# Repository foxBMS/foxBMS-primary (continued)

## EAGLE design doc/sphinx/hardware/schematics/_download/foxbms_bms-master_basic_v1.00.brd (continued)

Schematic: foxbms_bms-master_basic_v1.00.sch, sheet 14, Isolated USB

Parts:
C1401, C1406: 4.7µ; C0603
C1402, C1403, C1404, C1405, C1407, C1408, C1409, C1410: 100n; C0603
IC1401, IC1404: IP4220CZ6; D_SMD_TSOP6_(SOT457/SC-74)_R_NXP_REV01
IC1402, IC1405: FT231XS-R; IC_SMD_SSOP-20_R_FTDI_REV01
IC1403, IC1406: ADUM1401ARW; IC_SMD_SOIC-16_(JEDEC_MS-013-AA)_R_ANALOG_REV01
R1401, R1402, R1405, R1406: 27; 0603
R1403, R1404, R1407, R1408: 0; 0603
X1401, X1402: MINI-USB-2.0; X_SMD_MINI-USB-2.0-TYPAB_R_MULTICOMP_REV01

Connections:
+3.3V_0: C1405.1, IC1403.10 (VE2), IC1403.16 (VDD2); also elsewhere on the board
+3.3V_1: C1410.1, IC1406.10 (VE2), IC1406.16 (VDD2); also elsewhere on the board
DM: IC1401.4 (I/O3), R1401.2, X1401.2
DM1: IC1404.4 (I/O3), R1405.2, X1402.2
DP: IC1401.6 (I/O4), R1402.2, X1401.3
DP1: IC1404.6 (I/O4), R1406.2, X1402.3
FTDI_MCU_0_DTR: IC1403.13 (VOB); also elsewhere on the board
FTDI_MCU_0_RTS: IC1403.14 (VOA); also elsewhere on the board
FTDI_MCU_0_RX: IC1403.12 (VOC); also elsewhere on the board
FTDI_MCU_0_TX: IC1403.11 (VID); also elsewhere on the board
FTDI_MCU_1_DTR: IC1406.13 (VOB); also elsewhere on the board
FTDI_MCU_1_RTS: IC1406.14 (VOA); also elsewhere on the board
FTDI_MCU_1_RX: IC1406.12 (VOC); also elsewhere on the board
FTDI_MCU_1_TX: IC1406.11 (VID); also elsewhere on the board
GND_0: C1405.2, IC1403.9 (GND2), IC1403.15 (GND2); also elsewhere on the board
GND_1: C1410.2, IC1406.9 (GND2), IC1406.15 (GND2); also elsewhere on the board
unnamed: IC1402.11 (USBDP), R1402.1
unnamed: IC1402.12 (USBDM), R1401.1
unnamed: IC1405.11 (USBDP), R1406.1
unnamed: IC1405.12 (USBDM), R1405.1
unnamed: IC1402.20 (TXD), IC1403.5 (VIC)
unnamed: IC1405.20 (TXD), IC1406.5 (VIC)
unnamed: IC1405.4 (RXD), IC1406.6 (VOD)
unnamed: IC1405.2 (RTS#), IC1406.3 (VIA)
unnamed: IC1405.1 (DTR#), IC1406.4 (VIB)
unnamed: IC1402.4 (RXD), IC1403.6 (VOD)
unnamed: IC1402.1 (DTR#), IC1403.4 (VIB)
unnamed: C1409.1, IC1405.3 (VCCIO), IC1405.13 (3V3OUT), IC1405.14 (RESET#)
unnamed: IC1405.9 (CTS#), R1407.1
unnamed: IC1402.2 (RTS#), IC1403.3 (VIA)
unnamed: IC1405.7 (DSR#), R1408.1
unnamed: IC1402.9 (CTS#), R1403.1
unnamed: IC1402.7 (DSR#), R1404.1
USB_0_GND_EXT: C1401.2, C1402.2, C1403.2, C1404.2, IC1401.2 (GND), IC1402.6 (GND1), IC1402.16 (GND2), IC1403.2 (GND1), IC1403.8 (GND1), R1403.2, R1404.2, X1401.5
USB_0_VBUS1_EXT: C1401.1, C1402.1, C1403.1, IC1401.5 (VP), IC1402.15 (VCC), IC1403.1 (VDD1), IC1403.7 (VE1), X1401.1
USB_0_VCC_EXT: C1404.1, IC1402.3 (VCCIO), IC1402.13 (3V3OUT), IC1402.14 (RESET#)
USB_GND_0_EXT1: C1406.2, C1407.2, C1408.2, C1409.2, IC1404.2 (GND), IC1405.6 (GND1), IC1405.16 (GND2), IC1406.2 (GND1), IC1406.8 (GND1), R1407.2, R1408.2, X1402.5
USB_VBUS1_0_EXT1: C1406.1, C1407.1, C1408.1, IC1404.5 (VP), IC1405.15 (VCC), IC1406.1 (VDD1), IC1406.7 (VE1), X1402.1

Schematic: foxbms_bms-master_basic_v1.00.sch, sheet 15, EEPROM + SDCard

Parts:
C1501: 100n; 0603
IC1501: AT25128B-SSHL-T; IC_SMD_SOIC-8_R_ATMEL_REV01
R1501, R1502: 10k; 0603

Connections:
+3.3V_0: C1501.2, IC1501.8 (VCC), R1501.2, R1502.2; also elsewhere on the board
DATA_STORAGE_SPI_EEPROM_CS: IC1501.1 (!CS); also elsewhere on the board
DATA_STORAGE_SPI_MISO: IC1501.2 (SO); also elsewhere on the board
DATA_STORAGE_SPI_MOSI: IC1501.5 (SI); also elsewhere on the board
DATA_STORAGE_SPI_SCK: IC1501.6 (SCK); also elsewhere on the board
GND_0: C1501.1, IC1501.4 (GND); also elsewhere on the board
unnamed: IC1501.7 (HOLD), R1501.1
unnamed: IC1501.3 (!WP), R1502.1

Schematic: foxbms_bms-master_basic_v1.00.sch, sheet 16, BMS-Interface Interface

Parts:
C1601, C1602, C1603, C1604: 100n; C0603
SV1601, SV1603: MA04-2
SV1602, SV1604: MA08-2
X1601: 43045-1600_MOLEX_16PIN; X_TH_MOLEX_43045-1600_R_REV01

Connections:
+3.3V_0: C1601.1, SV1602.3; also elsewhere on the board
+3.3V_1: C1603.1, SV1604.3; also elsewhere on the board
+5.0V_0: C1602.1, SV1602.4; also elsewhere on the board
+5.0V_1: C1604.1, SV1604.4; also elsewhere on the board
BMS-INTERFACE_0_GPIO_0: SV1602.11; also elsewhere on the board
BMS-INTERFACE_0_GPIO_1: SV1602.12; also elsewhere on the board
BMS-INTERFACE_0_GPIO_2: SV1602.2; also elsewhere on the board
BMS-INTERFACE_0_GPIO_3: SV1602.1; also elsewhere on the board
BMS-INTERFACE_0_SPI_CS: SV1602.8; also elsewhere on the board
BMS-INTERFACE_0_SPI_MISO: SV1602.6; also elsewhere on the board
BMS-INTERFACE_0_SPI_MOSI: SV1602.5; also elsewhere on the board
BMS-INTERFACE_0_SPI_SCK: SV1602.7; also elsewhere on the board
BMS-INTERFACE_1_GPIO_0: SV1604.11; also elsewhere on the board
BMS-INTERFACE_1_GPIO_1: SV1604.12; also elsewhere on the board
BMS-INTERFACE_1_GPIO_2: SV1604.2; also elsewhere on the board
BMS-INTERFACE_1_GPIO_3: SV1604.1; also elsewhere on the board
BMS-INTERFACE_1_SPI_CS: SV1604.8; also elsewhere on the board
BMS-INTERFACE_1_SPI_MISO: SV1604.6; also elsewhere on the board
BMS-INTERFACE_1_SPI_MOSI: SV1604.5; also elsewhere on the board
BMS-INTERFACE_1_SPI_SCK: SV1604.7; also elsewhere on the board
GND_0: C1601.2, C1602.2, SV1602.9, SV1602.10; also elsewhere on the board
GND_1: C1603.2, C1604.2, SV1604.9, SV1604.10; also elsewhere on the board
unnamed: SV1601.1, X1601.1
unnamed: SV1601.2, X1601.9
unnamed: SV1601.3, X1601.2
unnamed: SV1601.4, X1601.10
unnamed: SV1601.5, X1601.3
unnamed: SV1601.6, X1601.11
unnamed: SV1601.7, X1601.4
unnamed: SV1601.8, X1601.12
unnamed: SV1603.1, X1601.5
unnamed: SV1603.3, X1601.6
unnamed: SV1603.5, X1601.7
unnamed: SV1603.7, X1601.8
unnamed: SV1603.2, X1601.13
unnamed: SV1603.4, X1601.14
unnamed: SV1603.6, X1601.15
unnamed: SV1603.8, X1601.16

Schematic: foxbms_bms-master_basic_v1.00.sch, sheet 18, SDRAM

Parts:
C1801, C1802, C1803, C1804, C1805, C1806, C1807: 100n; C0603
IC1801: IS42S16400J-5TL; IC_SMD_TSOP-II_(54-PIN)_R_ISSI_REV01

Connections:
+3.3V_0: C1801.1, C1802.1, C1803.1, C1804.1, C1805.1, C1806.1, C1807.1, IC1801.1 (VDD), IC1801.3 (VDDQ), IC1801.9 (VDDQ), IC1801.14 (VDD), IC1801.27 (VDD), IC1801.43 (VDDQ), IC1801.49 (VDDQ); also elsewhere on the board
FMC_MCU_0_RAM_A0: IC1801.23 (A0); also elsewhere on the board
FMC_MCU_0_RAM_A1: IC1801.24 (A1); also elsewhere on the board
FMC_MCU_0_RAM_A2: IC1801.25 (A2); also elsewhere on the board
FMC_MCU_0_RAM_A3: IC1801.26 (A3); also elsewhere on the board
FMC_MCU_0_RAM_A4: IC1801.29 (A4); also elsewhere on the board
FMC_MCU_0_RAM_A5: IC1801.30 (A5); also elsewhere on the board
FMC_MCU_0_RAM_A6: IC1801.31 (A6); also elsewhere on the board
FMC_MCU_0_RAM_A7: IC1801.32 (A7); also elsewhere on the board
FMC_MCU_0_RAM_A8: IC1801.33 (A8); also elsewhere on the board
FMC_MCU_0_RAM_A9: IC1801.34 (A9); also elsewhere on the board
FMC_MCU_0_RAM_A10: IC1801.22 (A10); also elsewhere on the board
FMC_MCU_0_RAM_A11: IC1801.35 (A11); also elsewhere on the board
FMC_MCU_0_RAM_BA0: IC1801.20 (BA0); also elsewhere on the board
FMC_MCU_0_RAM_BA1: IC1801.21 (BA1); also elsewhere on the board
FMC_MCU_0_RAM_D0: IC1801.2 (DQ0); also elsewhere on the board
FMC_MCU_0_RAM_D1: IC1801.4 (DQ1); also elsewhere on the board
FMC_MCU_0_RAM_D2: IC1801.5 (DQ2); also elsewhere on the board
FMC_MCU_0_RAM_D3: IC1801.7 (DQ3); also elsewhere on the board
FMC_MCU_0_RAM_D4: IC1801.8 (DQ4); also elsewhere on the board
FMC_MCU_0_RAM_D5: IC1801.10 (DQ5); also elsewhere on the board
FMC_MCU_0_RAM_D6: IC1801.11 (DQ6); also elsewhere on the board
FMC_MCU_0_RAM_D7: IC1801.13 (DQ7); also elsewhere on the board
FMC_MCU_0_RAM_D8: IC1801.42 (DQ8); also elsewhere on the board
FMC_MCU_0_RAM_D9: IC1801.44 (DQ9); also elsewhere on the board
FMC_MCU_0_RAM_D10: IC1801.45 (DQ10); also elsewhere on the board
FMC_MCU_0_RAM_D11: IC1801.47 (DQ11); also elsewhere on the board
FMC_MCU_0_RAM_D12: IC1801.48 (DQ12); also elsewhere on the board
FMC_MCU_0_RAM_D13: IC1801.50 (DQ13); also elsewhere on the board
FMC_MCU_0_RAM_D14: IC1801.51 (DQ14); also elsewhere on the board
FMC_MCU_0_RAM_D15: IC1801.53 (DQ15); also elsewhere on the board
FMC_MCU_0_RAM_NBL0: IC1801.15 (LDQM); also elsewhere on the board
FMC_MCU_0_RAM_NBL1: IC1801.39 (UDQM); also elsewhere on the board
FMC_MCU_0_RAM_SDCKE1: IC1801.37 (CKE); also elsewhere on the board
FMC_MCU_0_RAM_SDCLK: IC1801.38 (CLK); also elsewhere on the board
FMC_MCU_0_RAM_SDNCAS: IC1801.17 (!CAS); also elsewhere on the board
FMC_MCU_0_RAM_SDNE1: IC1801.19 (!CS); also elsewhere on the board
FMC_MCU_0_RAM_SDNRAS: IC1801.18 (!RAS); also elsewhere on the board
FMC_MCU_0_RAM_SDNWE: IC1801.16 (!WE); also elsewhere on the board
GND_0: C1801.2, C1802.2, C1803.2, C1804.2, C1805.2, C1806.2, C1807.2, IC1801.6 (GNDQ), IC1801.12 (GNDQ), IC1801.28 (GND), IC1801.41 (GND), IC1801.46 (GNDQ), IC1801.52 (GNDQ), IC1801.54 (GND); also elsewhere on the board

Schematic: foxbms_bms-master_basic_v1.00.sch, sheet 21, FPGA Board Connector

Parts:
C2101, C2102: 100n; C0603
SV2101: MA04-2

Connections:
+3.3V_0: C2101.2, SV2101.1; also elsewhere on the board
+5.0V_0: C2102.1, SV2101.2; also elsewhere on the board
GND_0: C2101.1, C2102.2, SV2101.5, SV2101.6; also elsewhere on the board
MCU_TO_FPGA_INTERFACE_MCU_0_CS: SV2101.8; also elsewhere on the board
MCU_TO_FPGA_INTERFACE_MCU_0_MISO: SV2101.3; also elsewhere on the board
MCU_TO_FPGA_INTERFACE_MCU_0_MOSI: SV2101.7; also elsewhere on the board
MCU_TO_FPGA_INTERFACE_MCU_0_SCK: SV2101.4; also elsewhere on the board

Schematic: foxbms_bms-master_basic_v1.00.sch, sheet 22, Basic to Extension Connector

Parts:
JP2201, JP2202: PINHD-2X12; 2X12

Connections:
+3.3V_0: JP2201.1, JP2201.3, JP2202.1, JP2202.3; also elsewhere on the board
ADC_MCU_0_CH_0: JP2202.8; also elsewhere on the board
ADC_MCU_0_CH_1: JP2202.7; also elsewhere on the board
ADC_MCU_0_CH_2: JP2202.6; also elsewhere on the board
ADC_MCU_0_CH_3: JP2202.5; also elsewhere on the board
ADC_MCU_0_CH_4: JP2202.9; also elsewhere on the board
CAN_1_RX: JP2201.6; also elsewhere on the board
CAN_1_TRANS_STANDBY_CONTROL: JP2201.5; also elsewhere on the board
CAN_1_TX: JP2201.7; also elsewhere on the board
CONTACTOR_6_CONTROL: JP2201.18; also elsewhere on the board
CONTACTOR_6_FEEDBACK: JP2201.17; also elsewhere on the board
CONTACTOR_7_CONTROL: JP2201.16; also elsewhere on the board
CONTACTOR_7_FEEDBACK: JP2201.15; also elsewhere on the board
CONTACTOR_8_CONTROL: JP2202.10; also elsewhere on the board
CONTACTOR_8_FEEDBACK: JP2202.11; also elsewhere on the board
DATA_STORAGE_SPI_MISO: JP2201.21; also elsewhere on the board
DATA_STORAGE_SPI_MOSI: JP2201.19; also elsewhere on the board
DATA_STORAGE_SPI_SCK: JP2201.20; also elsewhere on the board
DATA_STORAGE_SPI_SDCARD_NSS: JP2201.23; also elsewhere on the board
GND_0: JP2201.2, JP2201.4, JP2202.2, JP2202.4; also elsewhere on the board
ISONOC_0_CONTROL: JP2202.16; also elsewhere on the board
ISONOC_1_CONTROL: JP2202.17; also elsewhere on the board
ISONOC_2_CONTROL: JP2202.18; also elsewhere on the board
ISONOC_3_CONTROL: JP2202.19; also elsewhere on the board
ISONOC_4_CONTROL: JP2202.20; also elsewhere on the board
ISONOC_5_CONTROL: JP2202.21; also elsewhere on the board
ISO_GPIO_MCU_0_IN_0: JP2202.22; also elsewhere on the board
ISO_GPIO_MCU_0_IN_1: JP2202.23; also elsewhere on the board
ISO_GPIO_MCU_0_IN_2: JP2201.13; also elsewhere on the board
ISO_GPIO_MCU_0_IN_3: JP2201.10; also elsewhere on the board
ISO_GPIO_MCU_0_OUT_0: JP2201.9; also elsewhere on the board
ISO_GPIO_MCU_0_OUT_1: JP2201.14; also elsewhere on the board
ISO_GPIO_MCU_0_OUT_2: JP2201.11; also elsewhere on the board
ISO_GPIO_MCU_0_OUT_3: JP2201.12; also elsewhere on the board
RS485_MCU_0_DE: JP2202.15; also elsewhere on the board
RS485_MCU_0_NRE: JP2202.14; also elsewhere on the board
RS485_MCU_0_RX: JP2202.13; also elsewhere on the board
RS485_MCU_0_TX: JP2202.12; also elsewhere on the board
SDCARD_SUPPLY_CONTROL: JP2201.22; also elsewhere on the board

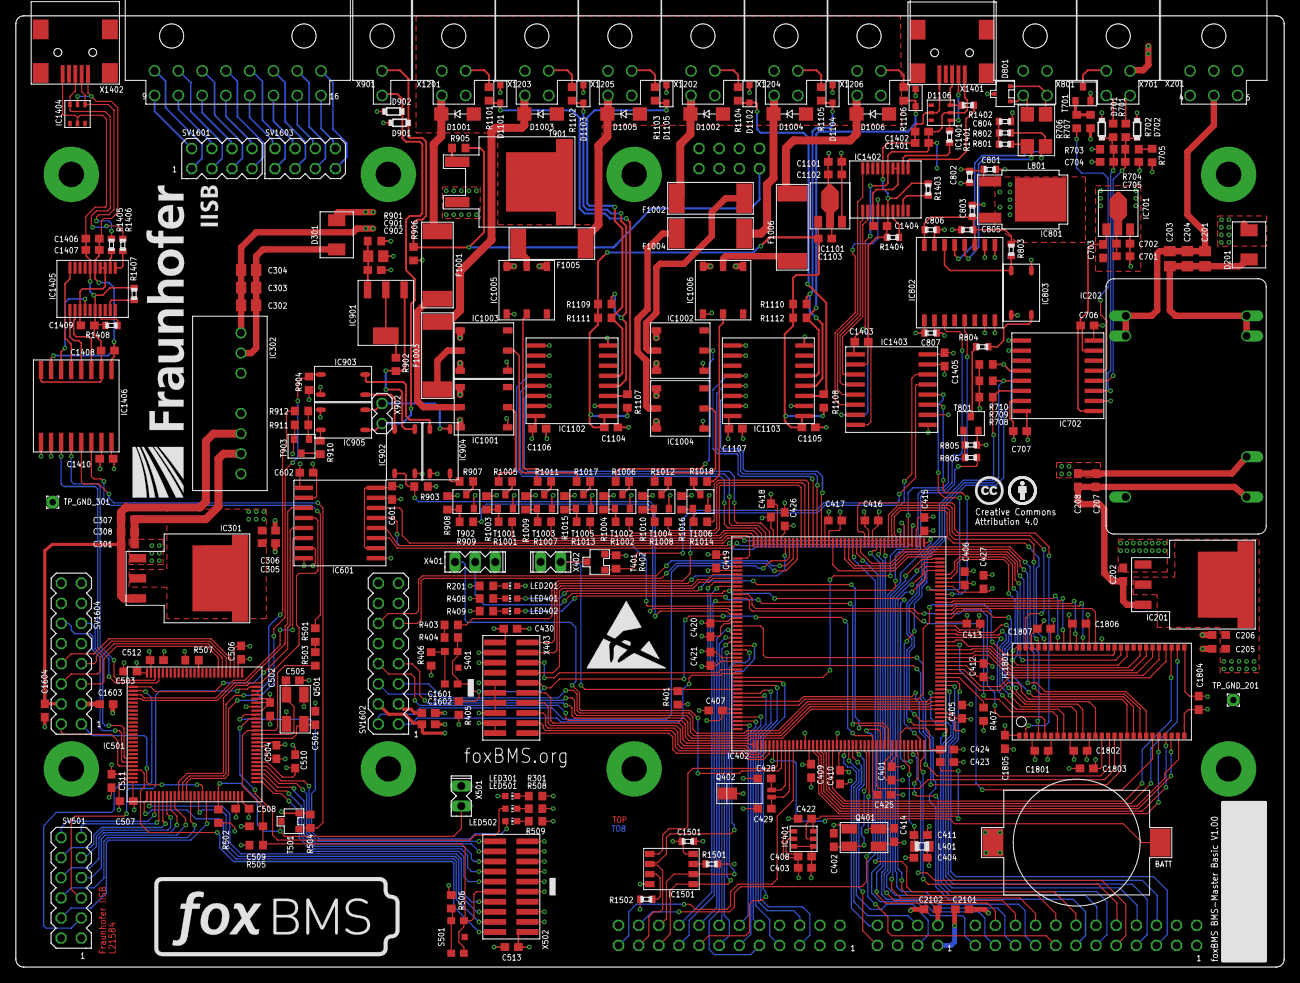
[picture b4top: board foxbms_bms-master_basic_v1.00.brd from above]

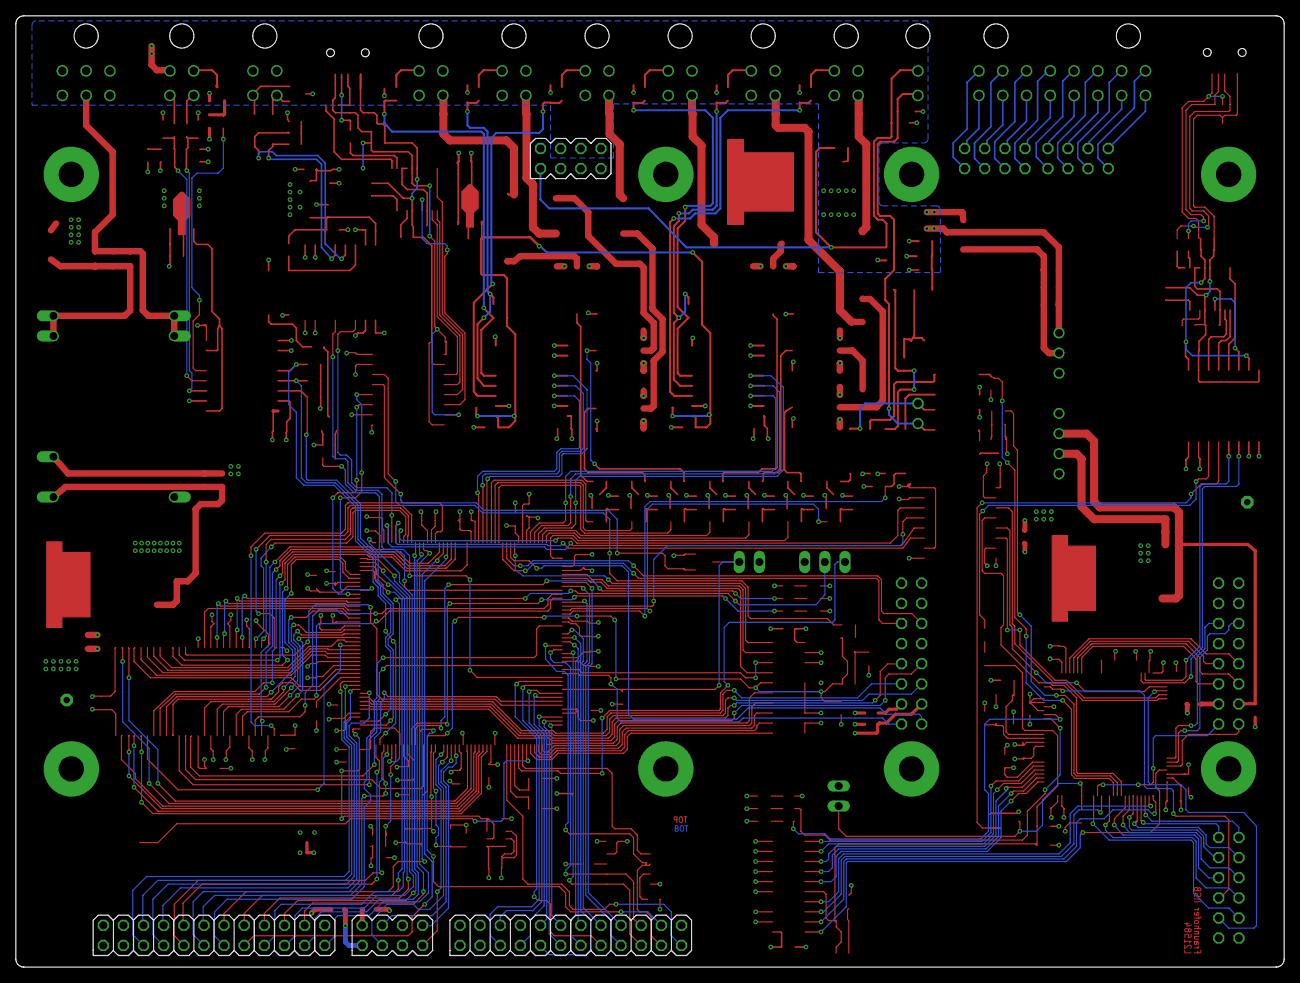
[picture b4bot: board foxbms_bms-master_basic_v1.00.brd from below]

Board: 4 copper layers, 160.0 x 120.0 mm, 314 parts (4 on the bottom side), 331 nets.

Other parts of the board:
U$2: ESD_10.00

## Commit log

2017-02-01 Adding foxBMS documentation
2017-02-03 Changelog =============================
    0.4.3
    ----------
    - Important: Changed contactor configuration order in the software to match the labels on the front
    - Contactor 0: CONT_PLUS_MAIN
    - Contactor 1: CONT_PLUS_PRECHARGE
    - Contactor 2: CONT_MINUS_MAIN
2017-02-03 Renamed files in hardware documentation to match lowercase guideline
2017-02-07 Removed layout and schematic files from documentation as they have their own repository.
2017-02-08 Remove unnecessary files.
2017-02-10 Reduce size of pictures in documentation.
2017-02-13 Added license file (same license as already found in the documentation).
2017-02-28 Fixed waf binary.
2017-03-03 Update in documentation.
2017-03-17 Modify formatting in README.md
2017-03-31 Fixed checksum tool chain: replaced hard coded addresses in *.c/*.h files with relative ones.
2017-04-27 Correction in documentation in "Recommended Additional Hardware" part.
2017-04-28 Correction in documentation in part on current sensor configuration.
2017-05-09 Minor corrections (Lorentz)
2017-05-11 Improved checksum process - faster implementation of checksum script - checksum script is called automatically after "python tools/waf-1.8.12 configure build" - Build command "python tools/waf-1.8.12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
2017-05-12 Updated documentation.
2017-06-07 Updated LICENSE.md
2017-06-08 Updated foxBMS-primary sources to work with the new project structure --> Please read README.md for further information on working with the new project structure <--
2017-06-08 Added TravisCI support
2017-06-08 fixed TravisCI build
2017-06-09 Updated CHANGELOG.md
2017-08-29 updated CHANGELOG.md in master branch
2017-08-29 - updated year in the copyright - updated CHANGELOG.md - fixed markdown in LICENSE.md - minor changes in code and code cleanup - rewrite of the "eeprom"-module and moved to "nvram" - wscripts updated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
2017-08-29 fix git config error
2017-08-30 sync commit to release-0.5.1
2017-09-11 - updated CHANGELOG.md - fixed LTC temperature bug: We fixed a bug in the ltc driver, leading to a non-functional temperature sensing for foxBMS Slave Hardware version 1.xx. The slave version is conf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
2017-10-24 - update README.md - removed trailing whitespace
2017-12-01 Corrected function to select multiplexer channel in LTC. Corrected storage of soc value in non-volatile memory.
